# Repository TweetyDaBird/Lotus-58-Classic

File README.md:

### Notice! Files in the development branches are NOT intended for public use in production of PCB's, may or may not be tested and may change or be removed without notice! 
Please use the Gerber files for producing PCB's, found under the header 'Releases' instead. Also please note the difference between a 'Pre-release' (partially/fully untested, basically what I order a prototype PCB from to test) and a full actual 'Release' which is fully tested, built and ready to be used to produce PCB's.

That said, if you want to tweak/change or make something new based on my project, I can point you to a suitable starting point in the raw files. Talk to me, and I'm happy to help.
# Lotus 58 Glow

Starting with simple tweaks to the Lily58 Glow before ordering a set of PCB's it quickly spiraled out of control, and I ended up with what wasn't quite a Lily58 anymore, and although very similar in layout, it is no longer compatible with plate and case design. 

Because of this, it was renamed Lotus58, referencing another flower much like the lily in the name Lily58.

(photo from reddit by u/bduzik)

## General Specifications

- Layout very similar to the original Lily58 family
- Per key RGB and RGB underglow
- Kaihl Hot-swap sockets for MX compatible switches
- Can be used as a standalone Gamepad for either hand
- Optional 0.91" OLED Screens and rotary encoders (one each per side)
- All components through-hole and easily soldered for beginners (SMD option for diodes)
- Designed with a sandwich-style plate/case as part of the design

## Layout variations

- Optional plate layout with OLED screen (Encoder can be placed on upper thumb key position)
- Optional plate layout with rotary encoder (Removes OLED screen for that side)  
- Optional plate layout with no hole for OLED or upper encoder (Encoder can be placed on upper thumb key position)

## Things to note when ordering PCB's
### Finding the Gerber files
If you are not aiming at modifying things, don't look for the gerber files in the folders, pretty please!</BR>
And please don't open yet another issue about it! </BR>
The gerber files are where they belong, zipped up in releases, look under that header for the version you want.

### Tips & Tricks
- Most PCB manufacturers have a MOQ of 5 PCB's, meaning you end up with 2½ keyboards when finished.
- The recommended PCB thickness is 1.6 mm, both for the main PCB and plates to allow the keyswitches to grip the plate and lock in place securely.

If ordering from [JLCPCB](https://www.jlcpcb.com) the plate Gerber files include a reference putting the added serial etc on a breakaway part for a clean look with minimal cost, if using another manufacturer it's possible they have additional fee's for removing the extra text, or you should consider plotting the Gerber files yourself with the correct reference for your manufacturer. Otherwise use the standard settings from JLPCB.

## Buy a kit!
I sell complete kits, making it easy to build your keyboard, and it also supports prototypes for new wacky ones. 

## Discord for build help and discussions!

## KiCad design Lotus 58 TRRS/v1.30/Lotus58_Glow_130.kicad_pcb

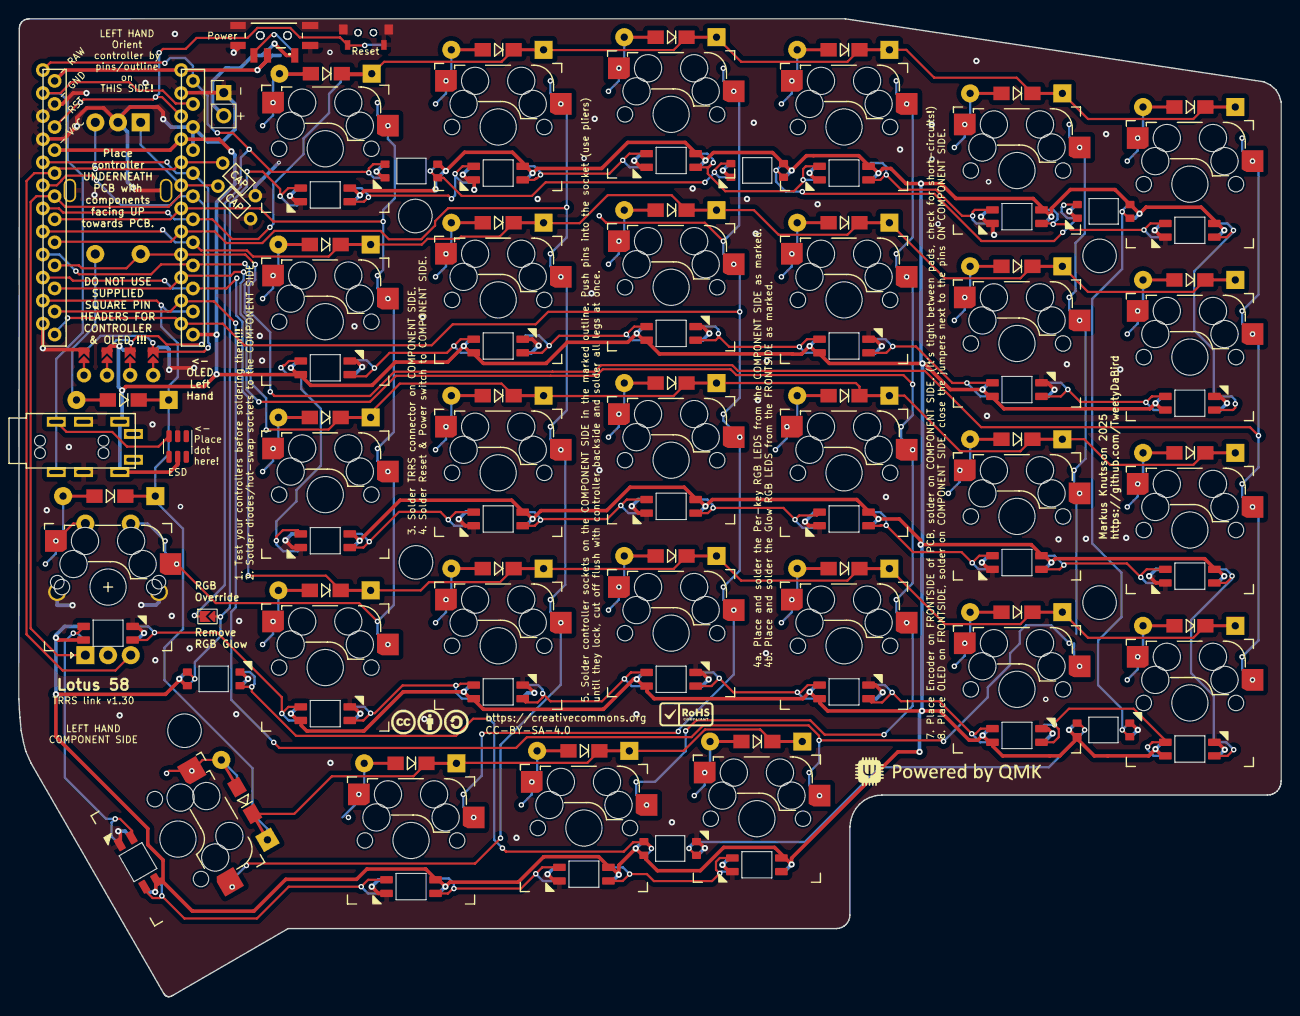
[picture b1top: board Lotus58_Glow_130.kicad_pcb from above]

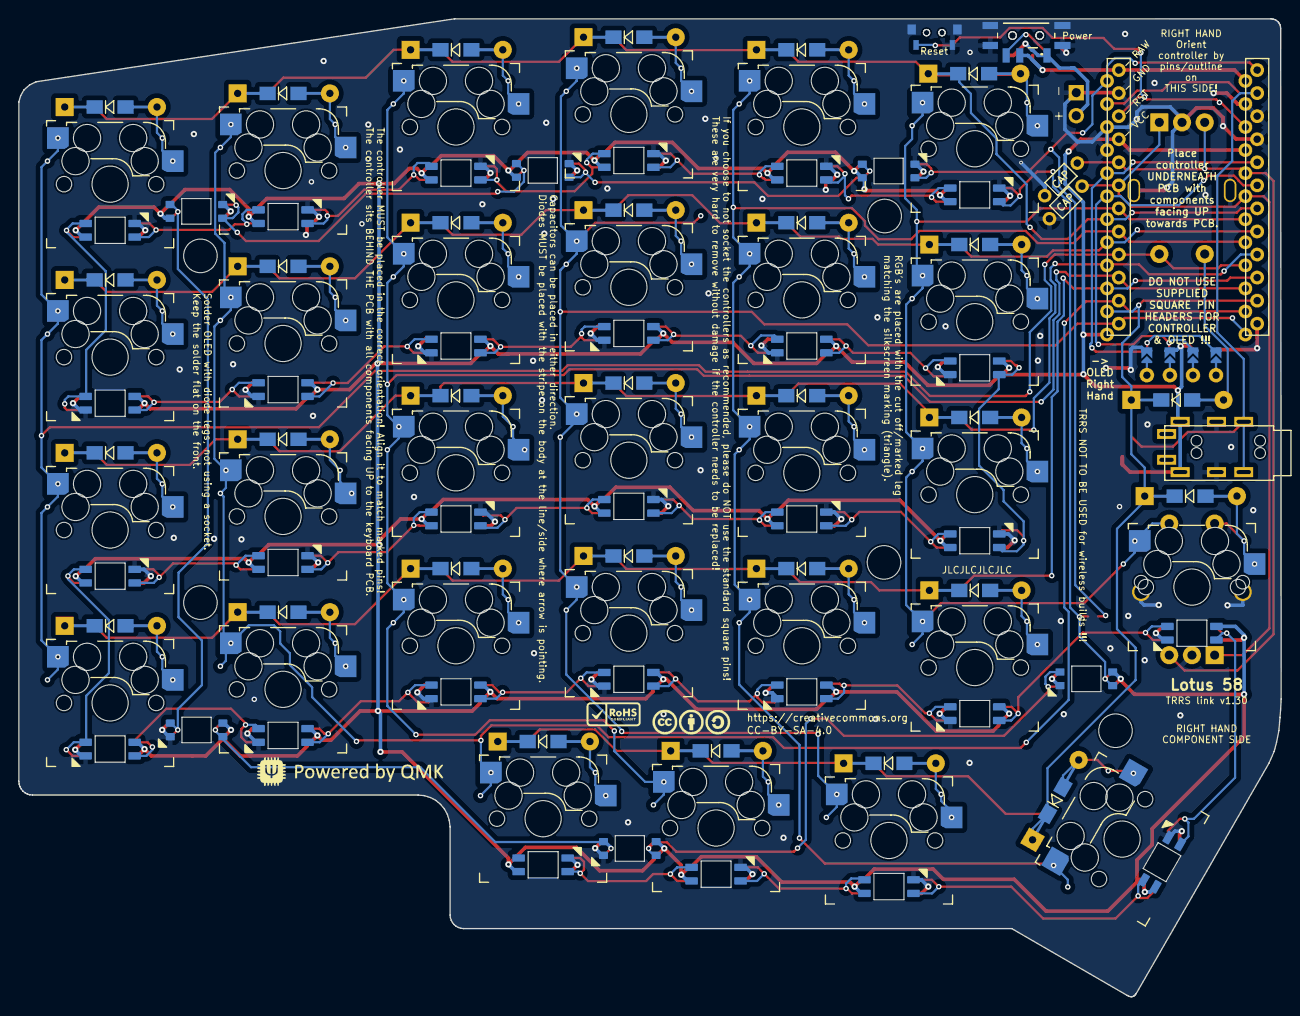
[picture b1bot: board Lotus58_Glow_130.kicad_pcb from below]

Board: 2 copper layers, 139.1 x 107.7 mm, 117 parts (70 on the bottom side), 86 nets.

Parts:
C1, C2: 50V/100nF axial; RESISTOR_Reversible
D1, D2, D3, D4, D5, D6, D7, D8, D9, D10, D11, D12, D13, D14, D15, D16, D17, D18, D19, D20, D21, D22, D23, D24, D25, D26, D27, D28, D29, D30: 1N4148/1N4148W; Diode_DO35_SOD123
J1: PJ-320A; MJ-4PP-9_alim
J2: Conn_01x02; PinHeader_1x02_P2.54mm_Vertical
JP5: FULL; Jumper_min_v2
LED1, LED2, LED3, LED4, LED5, LED6: SK6812MINI-E; MX_SK6812MINI-E_REVERSIBLE_special_v2
LED7, LED8, LED9, LED10, LED11, LED12, LED13, LED14, LED15, LED16, LED17, LED18, LED19, LED20, LED21, LED22, LED23, LED24, LED25, LED26, LED27, LED28, LED29, LED30, LED31, LED32, LED33, LED34, LED35: SK6803MINI-E; MX_SK6812MINI-E_REVERSIBLE
Logo1, Logo8: QMK_Logo; qmk logo
Logo2, Logo7: CC-BY-SA-4.0; CC_BY_SA_40_line
P1: OLED; SSD1306-0.91-OLED-4pin-128x32 doublesided
RES1, RES2: TS-A002; YTS-A002
S1, S2: MSK12C02
SW1, SW2, SW3, SW4, SW5, SW6, SW7, SW8, SW9, SW10, SW11, SW12, SW13, SW14, SW15, SW16, SW17, SW18, SW19, SW20, SW21, SW22, SW23, SW24, SW25, SW26, SW27, SW28, SW29: Kailh hotswap MX socket; SW_MX_HotSwap_Reversible
SW30: EC_11; RotaryEncoder_Alps_EC11E-Switch_Vertical_H20_special
SW31: EC_11; RotaryEncoder_Alps_EC11E-Switch_Special
TH1, TH2, TH3, TH4, TH5: HOLE; Spacer PCB hole
U1: Controller; ProMicro_Reversible_orig
U2: SRV05-4; SOT-23-6

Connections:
/Batt: J2.2, S1.NC, S2.NC
A: C2.2, SW30.A, SW31.A, U1.19 (A2/PF5)
Alt: D25.2 (A), SW25.2, SW31.S2
B: C1.2, SW30.B, SW31.B, U1.20 (A3/PF4)
Battery: S1.COM, S2.COM, U1.24 (RAW)
DATA: J1.R2, U1.2 (RX1/PD2), U2.3 (IO2)
GND: C1.1, C2.1, J1.R1, J2.1, LED1.3 (GND), LED2.3 (GND), LED3.3 (GND), LED4.3 (GND), LED5.3 (GND), LED6.3 (GND), LED7.3 (GND), LED8.3 (GND), LED9.3 (GND), LED10.3 (GND), LED11.3 (GND), LED12.3 (GND), LED13.3 (GND), LED14.3 (GND), LED15.3 (GND), LED16.3 (GND), LED17.3 (GND), LED18.3 (GND), LED19.3 (GND), LED20.3 (GND), LED21.3 (GND), LED22.3 (GND), LED23.3 (GND), LED24.3 (GND), LED25.3 (GND), LED26.3 (GND), LED27.3 (GND), LED28.3 (GND), LED29.3 (GND), LED30.3 (GND), LED31.3 (GND), LED32.3 (GND), LED33.3 (GND), LED34.3 (GND), LED35.3 (GND), P1.1 (GND), RES1.2, RES1.3, RES2.2, RES2.3, S1.MP (GND), S2.MP (GND), SW30.C, SW30.MP1 (GND), SW30.MP2 (GND), SW31.C, SW31.MP1 (GND), SW31.MP2 (GND), U1.3 (GND), U1.4 (GND), U1.23 (GND), U2.2 (VN)
LED: JP5.1, LED1.4 (DIN), U1.1 (TX0/PD3)
unnamed: D1.2 (A), SW1.2
unnamed: D2.2 (A), SW2.2
unnamed: D3.2 (A), SW3.2
unnamed: D4.2 (A), SW4.2
unnamed: D5.2 (A), SW5.2
unnamed: D6.2 (A), SW6.2
unnamed: D7.2 (A), SW7.2
unnamed: D8.2 (A), SW8.2
unnamed: D9.2 (A), SW9.2
unnamed: D10.2 (A), SW10.2
unnamed: D11.2 (A), SW11.2
unnamed: D12.2 (A), SW12.2
unnamed: D13.2 (A), SW13.2
unnamed: D14.2 (A), SW14.2
unnamed: D15.2 (A), SW15.2
unnamed: D16.2 (A), SW16.2
unnamed: D17.2 (A), SW17.2
unnamed: D18.2 (A), SW18.2
unnamed: D19.2 (A), SW19.2
unnamed: D20.2 (A), SW20.2
unnamed: D21.2 (A), SW21.2
unnamed: D22.2 (A), SW22.2
unnamed: D23.2 (A), SW23.2
unnamed: D24.2 (A), SW24.2
unnamed: D26.2 (A), SW26.2
unnamed: D27.2 (A), SW27.2
unnamed: D28.2 (A), SW28.2
unnamed: D29.2 (A), SW29.2
unnamed: D30.2 (A), SW30.S1
unnamed: LED1.2 (DOUT), LED2.4 (DIN)
unnamed: LED2.2 (DOUT), LED3.4 (DIN)
unnamed: LED3.2 (DOUT), LED4.4 (DIN)
unnamed: LED4.2 (DOUT), LED5.4 (DIN)
unnamed: LED5.2 (DOUT), LED6.4 (DIN)
unnamed: LED7.2 (DOUT), LED8.4 (DIN)
unnamed: LED8.2 (DOUT), LED9.4 (DIN)
unnamed: LED9.2 (DOUT), LED10.4 (DIN)
unnamed: LED10.2 (DOUT), LED11.4 (DIN)
unnamed: LED11.2 (DOUT), LED12.4 (DIN)
unnamed: LED12.2 (DOUT), LED18.4 (DIN)
unnamed: LED13.4 (DIN), LED14.2 (DOUT)
unnamed: LED13.2 (DOUT), LED19.4 (DIN)
unnamed: LED14.4 (DIN), LED15.2 (DOUT)
unnamed: LED15.4 (DIN), LED16.2 (DOUT)
unnamed: LED16.4 (DIN), LED17.2 (DOUT)
unnamed: LED17.4 (DIN), LED18.2 (DOUT)
unnamed: LED19.2 (DOUT), LED20.4 (DIN)
unnamed: LED20.2 (DOUT), LED21.4 (DIN)
unnamed: LED21.2 (DOUT), LED22.4 (DIN)
unnamed: LED22.2 (DOUT), LED23.4 (DIN)
unnamed: LED23.2 (DOUT), LED24.4 (DIN)
unnamed: LED24.2 (DOUT), LED30.4 (DIN)
unnamed: LED25.4 (DIN), LED26.2 (DOUT)
unnamed: LED25.2 (DOUT), LED31.4 (DIN)
unnamed: LED26.4 (DIN), LED27.2 (DOUT)
unnamed: LED27.4 (DIN), LED28.2 (DOUT)
unnamed: LED28.4 (DIN), LED29.2 (DOUT)
unnamed: LED29.4 (DIN), LED30.2 (DOUT)
unnamed: LED31.2 (DOUT), LED32.4 (DIN)
unnamed: LED32.2 (DOUT), LED33.4 (DIN)
unnamed: LED33.2 (DOUT), LED34.4 (DIN)
unnamed: LED34.2 (DOUT), LED35.4 (DIN)
RESET: RES1.1, RES2.1, U1.22 (RST)
RGB_LINK: JP5.2, LED6.2 (DOUT), LED7.4 (DIN)
SCL: P1.3 (SCL), U1.6 (3/PD0)
SDA: P1.4 (SDA), U1.5 (2/PD1)
VCC: J1.T, LED1.1 (VCC), LED2.1 (VCC), LED3.1 (VCC), LED4.1 (VCC), LED5.1 (VCC), LED6.1 (VCC), LED7.1 (VCC), LED8.1 (VCC), LED9.1 (VCC), LED10.1 (VCC), LED11.1 (VCC), LED12.1 (VCC), LED13.1 (VCC), LED14.1 (VCC), LED15.1 (VCC), LED16.1 (VCC), LED17.1 (VCC), LED18.1 (VCC), LED19.1 (VCC), LED20.1 (VCC), LED21.1 (VCC), LED22.1 (VCC), LED23.1 (VCC), LED24.1 (VCC), LED25.1 (VCC), LED26.1 (VCC), LED27.1 (VCC), LED28.1 (VCC), LED29.1 (VCC), LED30.1 (VCC), LED31.1 (VCC), LED32.1 (VCC), LED33.1 (VCC), LED34.1 (VCC), LED35.1 (VCC), P1.2 (VCC), U1.21 (VCC), U2.5 (VP)
col0: SW6.1, SW12.1, SW18.1, SW24.1, SW30.S2, U1.16 (15/PB1)
col1: SW5.1, SW11.1, SW17.1, SW23.1, SW29.1, U1.14 (16/PB2)
col2: SW4.1, SW10.1, SW16.1, SW22.1, SW28.1, U1.15 (14/PB3)
col3: SW3.1, SW9.1, SW15.1, SW21.1, SW27.1, U1.13 (10/PB6)
col4: SW2.1, SW8.1, SW14.1, SW20.1, SW26.1, U1.17 (A0/PF7)
col5: SW1.1, SW7.1, SW13.1, SW19.1, SW25.1, SW31.S1, U1.18 (A1/PF6)
row0: D1.1 (K), D2.1 (K), D3.1 (K), D4.1 (K), D5.1 (K), D6.1 (K), U1.7 (4/PD4)
row1: D7.1 (K), D8.1 (K), D9.1 (K), D10.1 (K), D11.1 (K), D12.1 (K), U1.8 (5/PC6)
row2: D13.1 (K), D14.1 (K), D15.1 (K), D16.1 (K), D17.1 (K), D18.1 (K), U1.9 (6/PD7)
row3: D19.1 (K), D20.1 (K), D21.1 (K), D22.1 (K), D23.1 (K), D24.1 (K), U1.10 (7/PE6)
row4: D25.1 (K), D26.1 (K), D27.1 (K), D28.1 (K), D29.1 (K), D30.1 (K), U1.11 (8/PB4)

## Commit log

2021-02-14 Shortened the links
2021-02-14 Added gerbers for plates
2025-07-09 v1.23 file cleanup
    Added pdf
2025-08-01 TRRS v1.30

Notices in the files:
Lotus 58 TRRS/v1.30/Lotus58_Glow_130.kicad_pcb:
Licensed under Creative Commons BY-SA 4.0 International
